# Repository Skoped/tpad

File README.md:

```                                                                                                                                           __                              .___
_/  |_          ___________     __| _/
\   __\  ______ \____ \__  \   / __ | 
 |  |   /_____/ |  |_> > __ \_/ /_/ | 
 |__|           |   __(____  /\____ | 
                |__|       \/      \/                                                                                                                                            
```
<sub> just a hackpad but better </sub>

so im made this macropad as a challenge, and it did NOT go well.
made this repo to show yall my progress   <sub> (its only made to submit this project) </sub>    i also couldnt make the knob work because i originally had the wrong 3d model for the rotary encoder.. (i made the knob :D)
anyways ignore all that,
# features.
it has 6 keys, one of them acting as a gateway to the second layer. so it technically has the usage of 10 keys, which i put from f1 to f10 because i use a 60% keyboard and the f-row doesnt always work for some reason.
it has a knob that acts as a way to decrease/increase volume, and when that knob is toggled, it acts as a way to decrease/increase brightness.
the screen currently only shows what layer your mini keyboard is on, pretty useless but im gonna work on another usecase.
# the pcb.
<figure> <figcaption>the pcb</figcaption>  </figure> <figure> <figcaption>the schematics</figcaption>  </figure>

i made this thing using kicad and tried to make it as tidy as possible which obviously i failed at that. this was probably the easiest part but i kept going back to it because i really didnt do it correctly at first.
# the case.
<figure> <figcaption>case put together</figcaption>  </figure> <figure> <figcaption>case laid out</figcaption>  </figure>

the case consists of 2 parts, the top and the bottom. i made it so the screws can screw in from the bottom, so that they can be hidden. the top has some columns coming out of it so the screw can screw the screw in the columns through the holes in the bottom layer, holding the two parts together.
worst part of this entire thing, fusion360 was too hard and i decided to experiment a bit with different software. i went on an ipad and found the absolute best app for this (very expensive so i used the trial :D). the app is shapr3d, i couldnt use fusion mostly because im using it on a pc with no touchscreen, making it harder to design what i wanted exactly.
# the firmware.
wasnt hard, kmk is easy and has alot of documentation to help with it. hopefully i can someday be good enough at programming to make a gui interface for remapping the keys. i only used layers to add about double the functionality to the keyboard (sixth button changes the entire keymap, and when the knob is pressed it changes brightness instead of volume, i just thought it was a cool way to make this different)
# BOM.
6x Cherry MX Switches

6x through-hole 1N4148 diodes

1x Seeed Studios XIAO RP2040

1x 0.91" OLED display SSD1306

1x EC11 rotary encoder

4x Keycaps

4x M3x5x4 headset inserts

4x M3x16mm screws

1x Case (2 part build, top and bottom)

### dont recommend this but will definitely do it again. 0/10
 *pcb and schematics made in kicad, case made in shapr3d, and the firmware made using kmk*

 this is not over, the screen basically doesnt do anything (just shows current keyboard layer) currently so im looking forward to edit its usecase. i also really wanna make that gui app for remapping everything :D

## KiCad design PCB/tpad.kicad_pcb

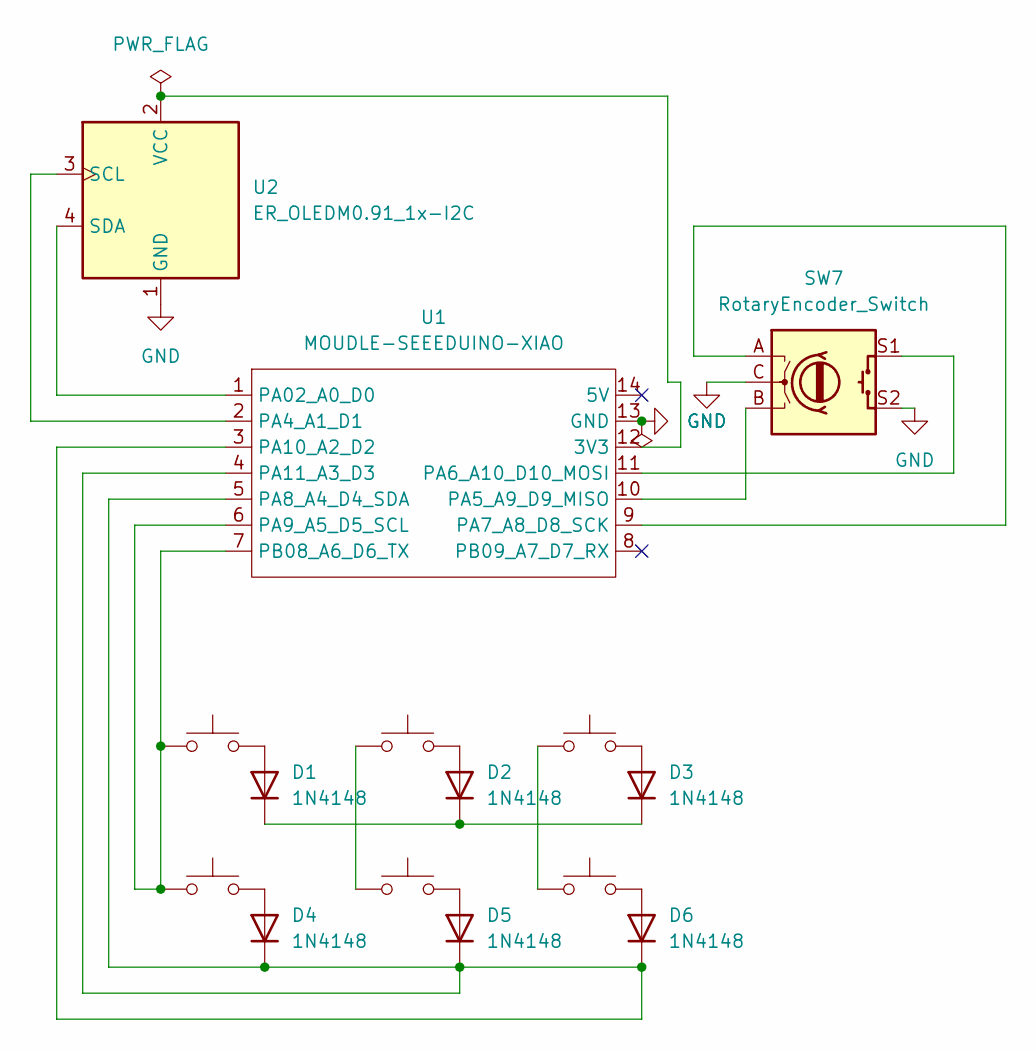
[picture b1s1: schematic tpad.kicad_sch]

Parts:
D1, D2, D3, D4, D5, D6: 1N4148; D_DO-35_SOD27_P7.62mm_Horizontal
SW1, SW2, SW3, SW4, SW5, SW6: SW_Push; SW_Cherry_MX_1.00u_PCB
SW7: RotaryEncoder_Switch; RotaryEncoder_Alps_EC11E-Switch_Vertical_H20mm
U1: MOUDLE-SEEEDUINO-XIAO; XIAO-Generic-Hybrid-14P-2.54-21X17.8MM
U2: ER_OLEDM0.91_1x-I2C

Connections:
GND: SW7.C, SW7.S2, U1.13 (GND), U2.1 (GND)
unnamed: D1.2 (A), SW1.2
unnamed: D1.1 (K), D2.1 (K), D3.1 (K)
unnamed: D2.2 (A), SW2.2
unnamed: D3.2 (A), SW3.2
unnamed: D4.2 (A), SW4.2
unnamed: D4.1 (K), D5.1 (K), D6.1 (K), U1.3 (PA10_A2_D2), U1.4 (PA11_A3_D3), U1.5 (PA8_A4_D4_SDA)
unnamed: D5.2 (A), SW5.2
unnamed: D6.2 (A), SW6.2
unnamed: SW2.1, SW5.1
unnamed: SW3.1, SW6.1
unnamed: U1.12 (3V3), U2.2 (VCC)
unnamed: U1.1 (PA02_A0_D0), U2.4 (SDA)
unnamed: U1.2 (PA4_A1_D1), U2.3 (SCL)
unnamed: SW7.B, U1.10 (PA5_A9_D9_MISO)
unnamed: SW7.S1, U1.11 (PA6_A10_D10_MOSI)
unnamed: SW7.A, U1.9 (PA7_A8_D8_SCK)
unnamed: SW1.1, SW4.1, U1.6 (PA9_A5_D5_SCL), U1.7 (PB08_A6_D6_TX)

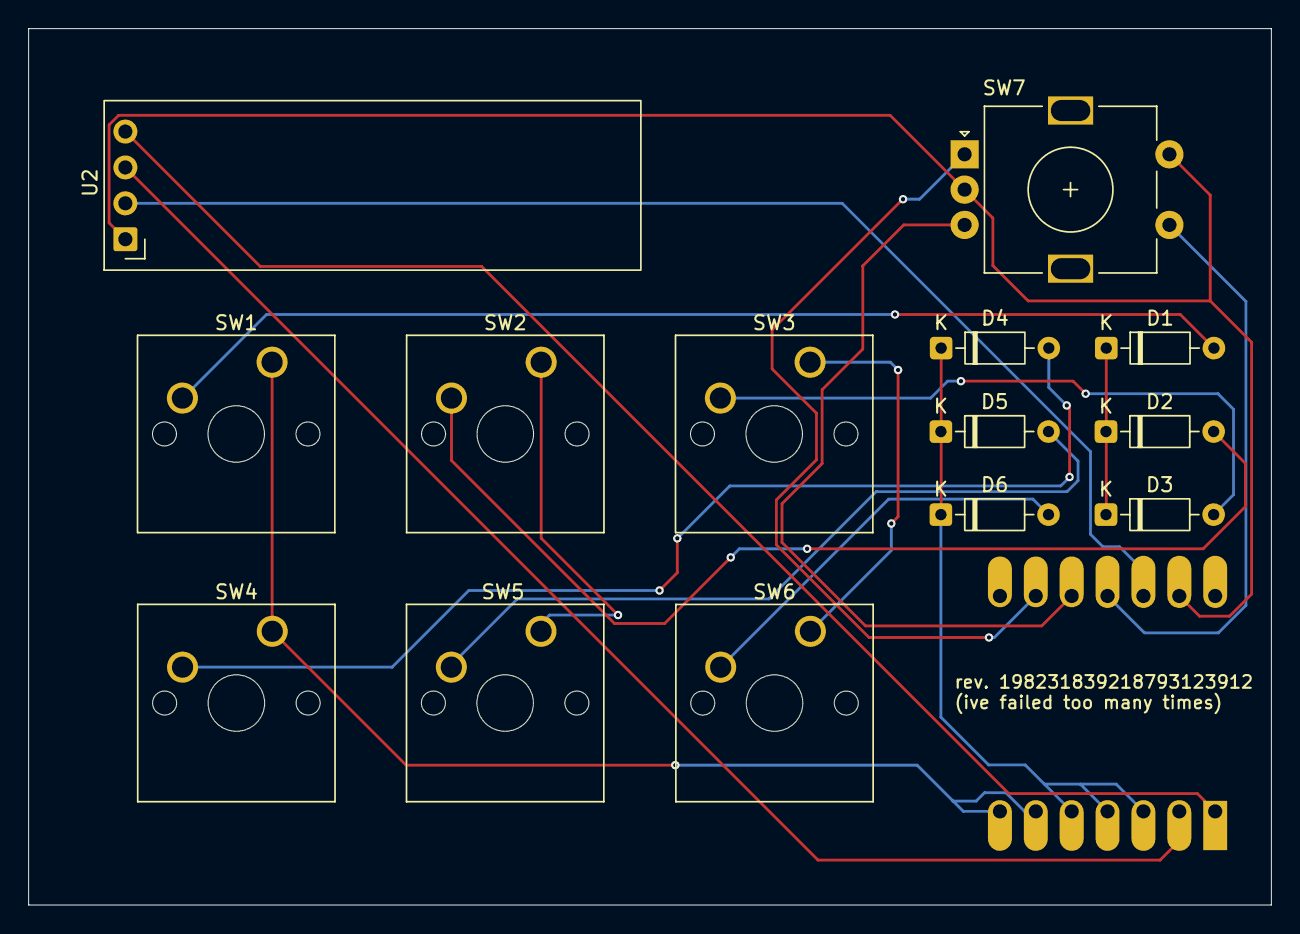
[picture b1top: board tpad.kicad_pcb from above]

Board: 2 copper layers, 88.0 x 62.1 mm, 15 parts (1 on the bottom side), 18 nets.

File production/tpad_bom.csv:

Designator,Footprint,Quantity,Value,LCSC Part #
"D1, D2, D3, D4, D5, D6",D_DO-35_SOD27_P7.62mm_Horizontal,6,1N4148,
"SW1, SW2, SW3, SW4, SW5, SW6",SW_Cherry_MX_1.00u_PCB,6,SW_Push,
SW7,RotaryEncoder_Alps_EC11E-Switch_Vertical_H20mm,1,RotaryEncoder_Switch,
U1,XIAO-Generic-Hybrid-14P-2.54-21X17.8MM,1,MOUDLE-SEEEDUINO-XIAO,
U2,ER_OLEDM0.91_1x-I2C,1,ER_OLEDM0.91_1x-I2C,
